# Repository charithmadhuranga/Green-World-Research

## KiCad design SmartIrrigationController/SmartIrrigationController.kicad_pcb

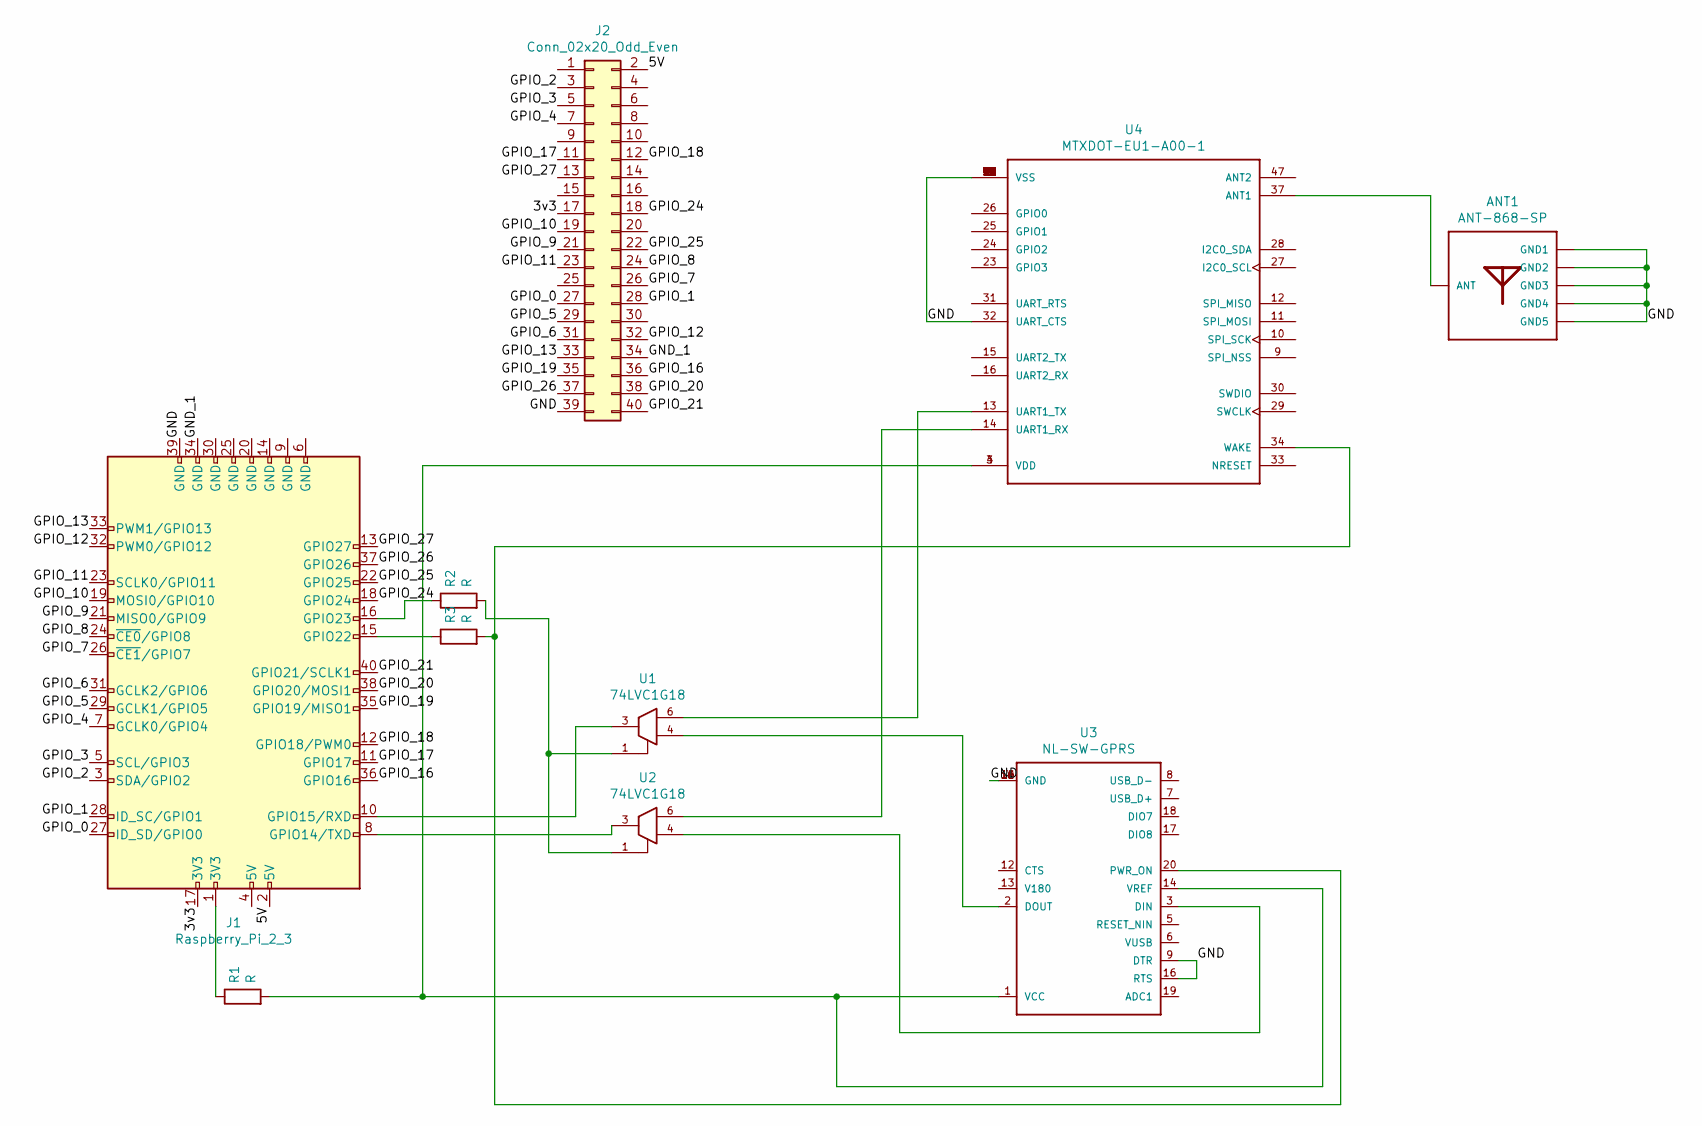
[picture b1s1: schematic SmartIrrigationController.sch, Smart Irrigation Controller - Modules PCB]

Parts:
ANT1: ANT-868-SP; ANT_868MHZ_SPLATCH
J1: Raspberry_Pi_2_3; PinSocket_2x20_P2.54mm_Vertical
J2: Conn_02x20_Odd_Even; PinHeader_2x20_P2.54mm_Vertical
R1, R2, R3: R; R_Axial_DIN0207_L6.3mm_D2.5mm_P10.16mm_Horizontal
U1, U2: 74LVC1G18
U3: NL-SW-GPRS; NIMBELINK_NL-SW-LTE-GELS3-C
U4: MTXDOT-EU1-A00-1; XCVR_MTXDOT-EU1-A00-1

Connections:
/3v3: J1.17 (3V3), J2.17
/5V: J1.2 (5V), J2.2
/GND_1: J1.34 (GND), J2.34
/GPIO_0: J1.27 (ID_SD/GPIO0), J2.27
/GPIO_1: J1.28 (ID_SC/GPIO1), J2.28
/GPIO_2: J1.3 (SDA/GPIO2), J2.3
/GPIO_3: J1.5 (SCL/GPIO3), J2.5
/GPIO_4: J1.7 (GCLK0/GPIO4), J2.7
/GPIO_5: J1.29 (GCLK1/GPIO5), J2.29
/GPIO_6: J1.31 (GCLK2/GPIO6), J2.31
/GPIO_7: J1.26 (~CE1~/GPIO7), J2.26
/GPIO_8: J1.24 (~CE0~/GPIO8), J2.24
/GPIO_9: J1.21 (MISO0/GPIO9), J2.21
/GPIO_10: J1.19 (MOSI0/GPIO10), J2.19
/GPIO_11: J1.23 (SCLK0/GPIO11), J2.23
/GPIO_12: J1.32 (PWM0/GPIO12), J2.32
/GPIO_13: J1.33 (PWM1/GPIO13), J2.33
/GPIO_16: J1.36 (GPIO16), J2.36
/GPIO_17: J1.11 (GPIO17), J2.11
/GPIO_18: J1.12 (GPIO18/PWM0), J2.12
/GPIO_19: J1.35 (GPIO19/MISO1), J2.35
/GPIO_20: J1.38 (GPIO20/MOSI1), J2.38
/GPIO_21: J1.40 (GPIO21/SCLK1), J2.40
/GPIO_24: J1.18 (GPIO24), J2.18
/GPIO_25: J1.22 (GPIO25), J2.22
/GPIO_26: J1.37 (GPIO26), J2.37
/GPIO_27: J1.13 (GPIO27), J2.13
GND: ANT1.GND1, ANT1.GND2, ANT1.GND3, ANT1.GND4, ANT1.GND5, J1.39 (GND), J2.39, U1.2 (GND), U2.2 (GND), U3.4 (GND), U3.9 (DTR), U3.10 (GND), U3.11 (GND), U3.15 (GND), U3.16 (RTS), U4.1 (VSS), U4.5 (VSS), U4.17 (VSS), U4.20 (VSS), U4.32 (UART_CTS), U4.35 (VSS), U4.36 (VSS), U4.38 (VSS), U4.39 (VSS), U4.40 (VSS), U4.41 (VSS), U4.42 (VSS), U4.43 (VSS), U4.44 (VSS), U4.45 (VSS), U4.46 (VSS), U4.48 (VSS), U4.49 (VSS), U4.50 (VSS), U4.51 (VSS), U4.52 (VSS), U4.53 (VSS), U4.54 (VSS), U4.55 (VSS), U4.56 (VSS), U4.57 (VSS), U4.58 (VSS)
unnamed: ANT1.MICROSTRIP (ANT), U4.37 (ANT1)
unnamed: J1.1 (3V3), R1.1
unnamed: J1.8 (GPIO14/TXD), U2.3
unnamed: J1.10 (GPIO15/RXD), U1.3
unnamed: J1.15 (GPIO22), R3.1
unnamed: J1.16 (GPIO23), R2.1
unnamed: R1.2, U3.1 (VCC), U3.14 (VREF), U4.3 (VDD), U4.4 (VDD)
unnamed: R2.2, U1.1, U2.1
unnamed: R3.2, U3.20 (PWR_ON), U4.34 (WAKE)
unnamed: U1.4, U3.2 (DOUT)
unnamed: U1.6, U4.13 (UART1_TX)
unnamed: U2.4, U3.3 (DIN)
unnamed: U2.6, U4.14 (UART1_RX)
VCC: U1.5 (VCC), U2.5 (VCC)

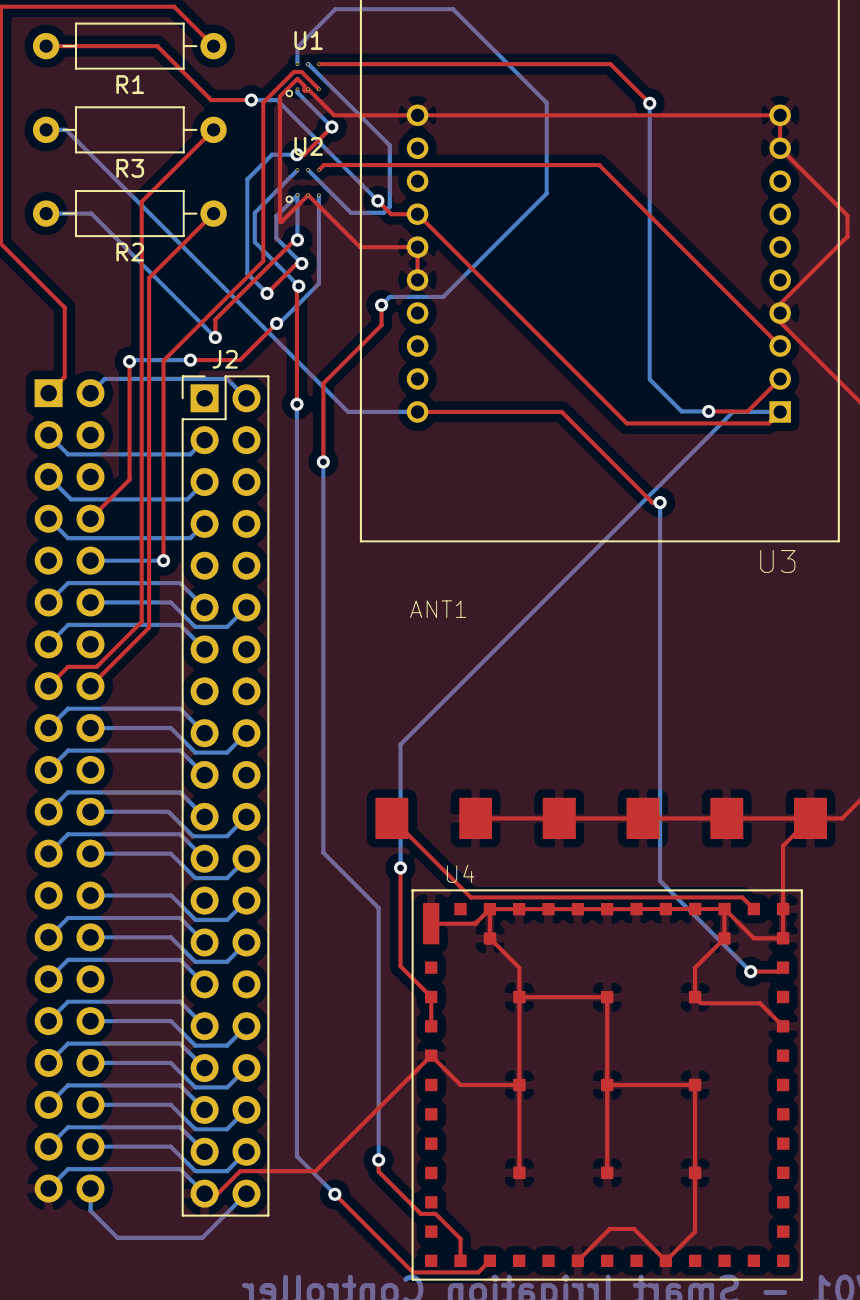
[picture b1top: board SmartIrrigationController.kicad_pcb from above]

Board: 2 copper layers, 10 parts (1 on the bottom side), 42 nets.

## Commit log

2021-11-04 Mycodo Enviromental controller
2021-11-04 add source for example
